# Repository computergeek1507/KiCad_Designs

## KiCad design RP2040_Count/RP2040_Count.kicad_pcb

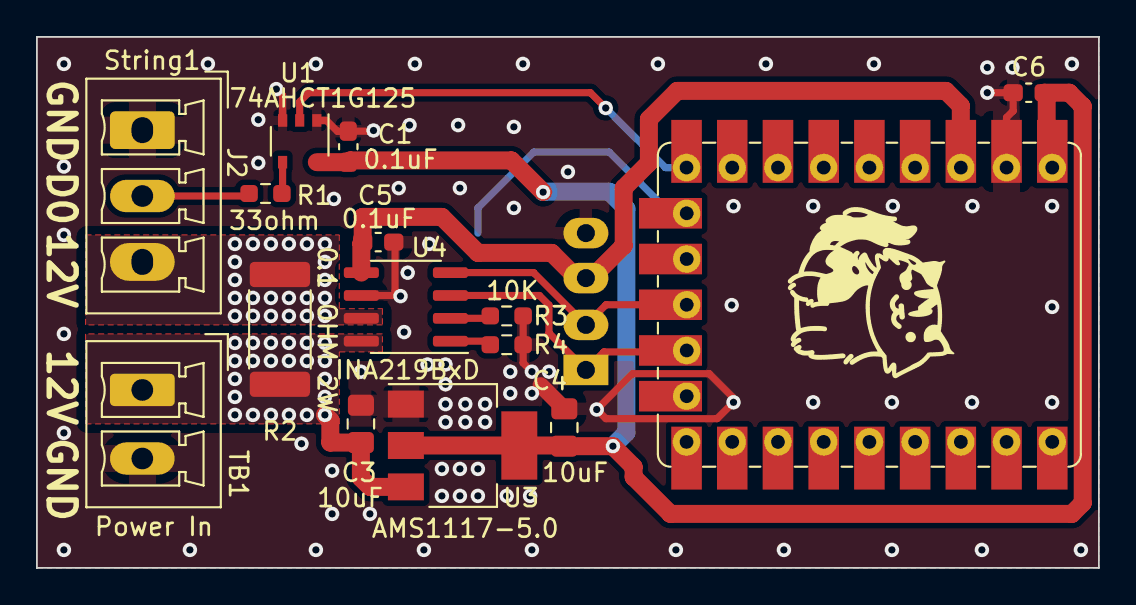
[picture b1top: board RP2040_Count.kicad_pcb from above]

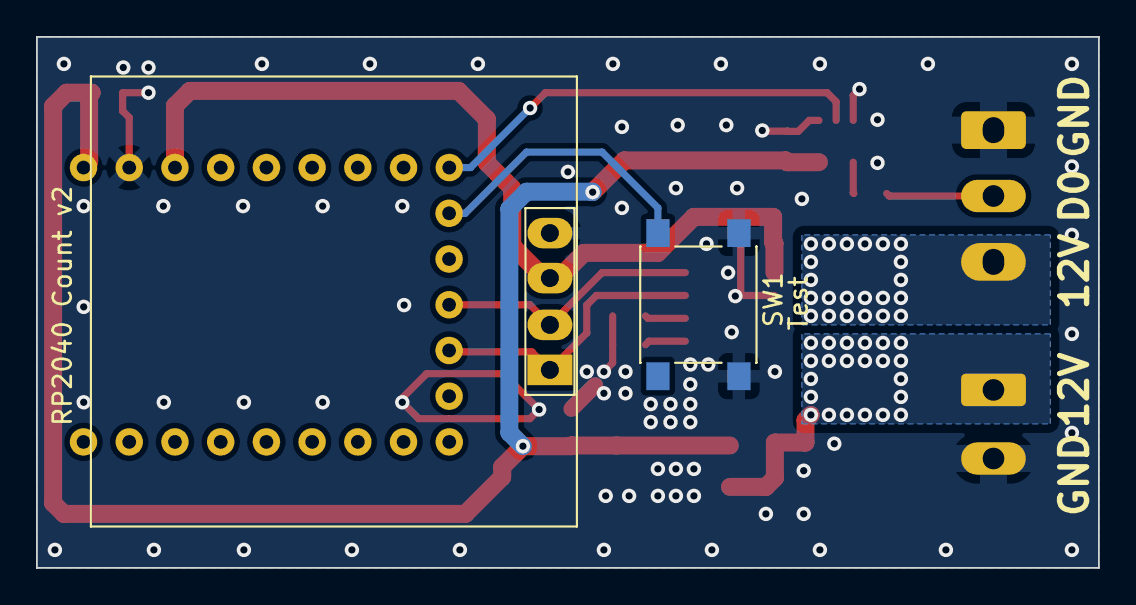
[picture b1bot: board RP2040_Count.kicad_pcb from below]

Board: 2 copper layers, 59.0 x 29.5 mm, 17 parts (2 on the bottom side), 13 nets.

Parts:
C1, C5, C6: 0.1uF; C_0603_1608Metric_Pad1.08x0.95mm_HandSolder
C3, C4: 10uF; C_0805_2012Metric_Pad1.18x1.45mm_HandSolder
J2: String1; PhoenixContact_MCV_3.81mm_3.5mm_1x03_Vertical
J3: OLED; OLED-SSD1306-128X64-I2C-THT_SCOTT2
R1: 33ohm; R_0603_1608Metric_Pad0.98x0.95mm_HandSolder
R2: 0.1 OHM 2W; R_2512_6332Metric_Pad1.40x3.35mm_HandSolder
R3, R4: 10K; R_0603_1608Metric_Pad0.98x0.95mm_HandSolder
SW1: Test; SW_Push_1P1T_NO_6x6mm_H9.5mm
TB1: Power In; PhoenixContact_MCV_1,5_2-G-3.81_1x02_P3.81mm_Vertical
U1: 74AHCT1G125; TSOP-5_1.65x3.05mm_P0.95mm
U3: AMS1117-5.0; SOT-223-3_TabPin2
U4: INA219BxD; SOIC-8_3.9x4.9mm_P1.27mm
U5: RP2040-Tiny; RP2040-Tiny_Scott

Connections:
+3.3V: C5.1, J3.3, U4.5 (VS), U5.3 (3V3)
+5V: C1.1, C4.1, C6.2, U1.5 (VCC), U3.2 (VO), U5.1 (5V)
/DOUT1: J2.2, R1.1
GND: C1.2, C3.2, C4.2, C5.2, C6.1, J2.1, J3.4, R3.2, R4.2, SW1.2, TB1.2, U1.1, U1.3 (GND), U3.1 (GND), U4.6 (GND), U5.2 (GND)
I2C_SCL: J3.2, U4.4 (SCL), U5.12 (GPIO11)
I2C_SDA: J3.1, U4.3 (SDA), U5.13 (GPIO10)
unnamed: R1.2, U1.4
unnamed: R3.1, U4.2 (A0)
unnamed: R4.1, U4.1 (A1)
OUT1: U1.2, U5.9 (GPIO14)
SW1: SW1.1, U5.10 (GPIO13)
VIN1: C3.1, R2.1, TB1.1, U3.3 (VI), U4.8 (IN+)
VOUT1: J2.3, R2.2, U4.7 (IN-)

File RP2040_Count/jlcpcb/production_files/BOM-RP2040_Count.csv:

Comment,Designator,Footprint,LCSC
INA219BxD,U4,SOIC-8_3.9x4.9mm_P1.27mm,C138706
0.1uF,"C1,C5,C6",C_0603_1608Metric_Pad1.08x0.95mm_HandSolder,C14663
10uF,"C3,C4",C_0805_2012Metric_Pad1.18x1.45mm_HandSolder,C15850
33ohm,R1,R_0603_1608Metric_Pad0.98x0.95mm_HandSolder,C23140
10K,"R3,R4",R_0603_1608Metric_Pad0.98x0.95mm_HandSolder,C25804
Test,SW1,SW_Push_1P1T_NO_6x6mm_H9.5mm,C2834918
0.1 OHM 2W,R2,R_2512_6332Metric_Pad1.40x3.35mm_HandSolder,C2903476
AMS1117-5.0,U3,SOT-223-3_TabPin2,C6187
74AHCT1G125,U1,TSOP-5_1.65x3.05mm_P0.95mm,C7484

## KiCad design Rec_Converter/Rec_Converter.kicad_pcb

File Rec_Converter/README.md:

# Copyright and Disclaimer
Copyright: Scott Hanson

This documentation describes Open Hardware and is licensed under the CERN OHL v. 1.2.

You may redistribute and modify this documentation under the terms of the CERN OHL v.1.2. (http://ohwr.org/cernohl). This documentation is distributed WITHOUT ANY EXPRESS OR IMPLIED WARRANTY, INCLUDING OF MERCHANTABILITY, SATISFACTORY QUALITY AND FITNESS FOR A PARTICULAR PURPOSE. Please see the CERN OHL v.1.2 for applicable conditions

# Rec Converter

Converter to use HolidayCoro dumb reciever with Falcon/Kulp Controllers and vice versa. The design was made with all through hole components for easy assembly by most users. Open source applications were used to create this controller. [KiCad](http://kicad-pcb.org/) was used for the PCB design, and [LibreOffice](https://www.libreoffice.org/) for the documentation.

To order your own PCB upload the gerber.zip file to your favorite PCB manufacture of choice, I personally use [jlcpcb.com](https://jlcpcb.com/).

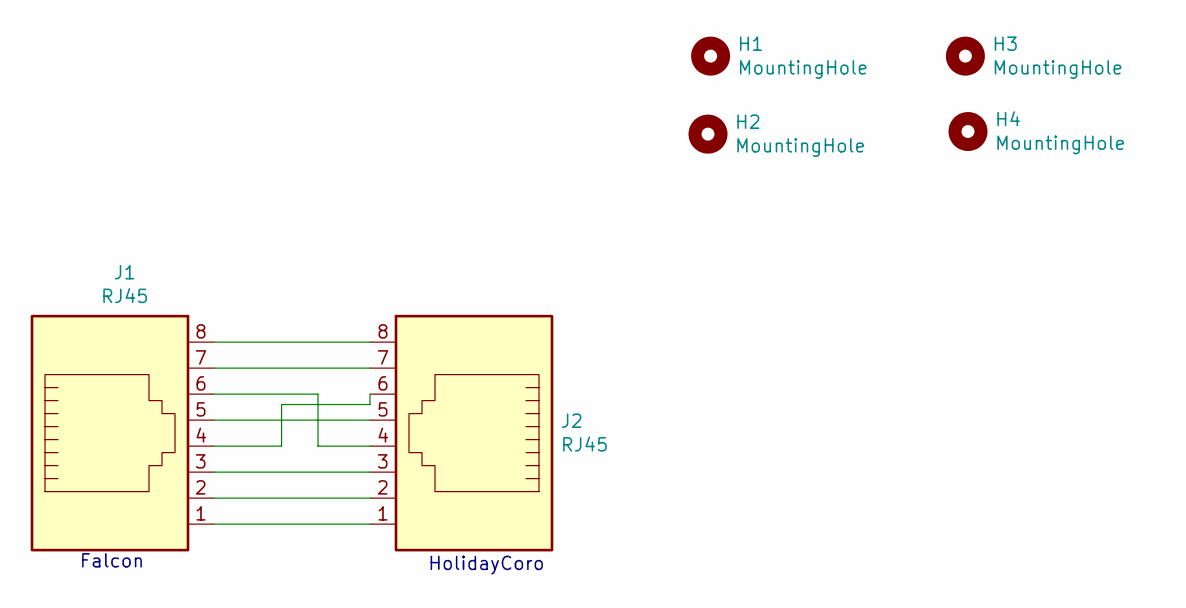
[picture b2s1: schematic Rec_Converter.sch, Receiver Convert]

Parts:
H1, H2, H3, H4: MountingHole; MountingHole_3.5mm
J1, J2: RJ45; RJ45_Amphenol_54602-x08_Horizontal; MPN A-2014-2-4-R; Digi-Key_PN AE10392-ND

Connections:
unnamed: J1.1, J2.1
unnamed: J1.2, J2.2
unnamed: J1.3, J2.3
unnamed: J1.4, J2.6
unnamed: J1.5, J2.5
unnamed: J1.6, J2.4
unnamed: J1.7, J2.7
unnamed: J1.8, J2.8

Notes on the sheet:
HolidayCoro
Falcon

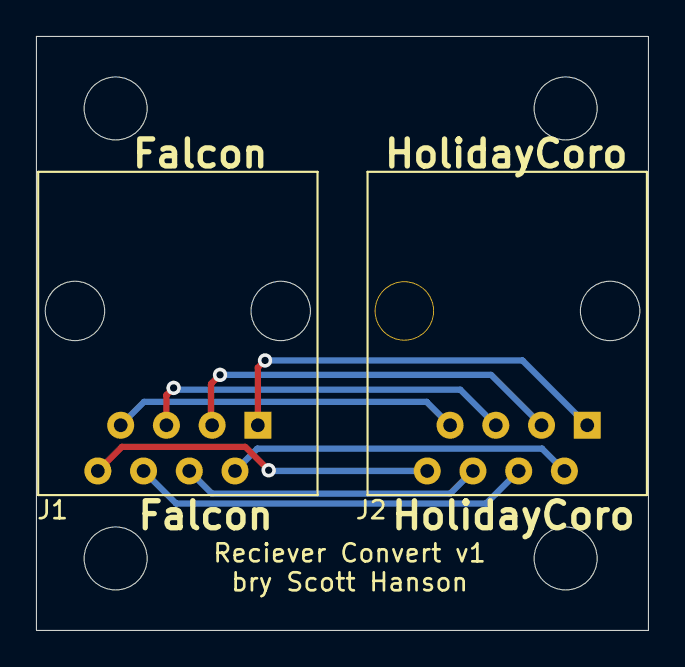
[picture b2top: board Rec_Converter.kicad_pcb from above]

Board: 2 copper layers, 34.0 x 33.0 mm, 6 parts (0 on the bottom side), 8 nets.

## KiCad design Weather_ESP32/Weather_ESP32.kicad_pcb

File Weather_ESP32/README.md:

# Copyright and Disclaimer
Copyright: Scott Hanson

This documentation describes Open Hardware and is licensed under the CERN OHL v. 1.2.

You may redistribute and modify this documentation under the terms of the CERN OHL v.1.2. (http://ohwr.org/cernohl). This documentation is distributed WITHOUT ANY EXPRESS OR IMPLIED WARRANTY, INCLUDING OF MERCHANTABILITY, SATISFACTORY QUALITY AND FITNESS FOR A PARTICULAR PURPOSE. Please see the CERN OHL v.1.2 for applicable conditions

# Weather ESP32

Breakout board for the WT32-ETH01 to use it with the [Sparkfun Weather Meter Kit](https://www.sparkfun.com/products/15901). The design was made with all through hole components for easy assembly by most users. Open source applications were used to create this controller. [KiCad](http://kicad-pcb.org/) was used for the PCB design, and [LibreOffice](https://www.libreoffice.org/) for the documentation.

To order your own PCB upload the gerber.zip file to your favorite PCB manufacture of choice, I personally use [jlcpcb.com](https://jlcpcb.com/).

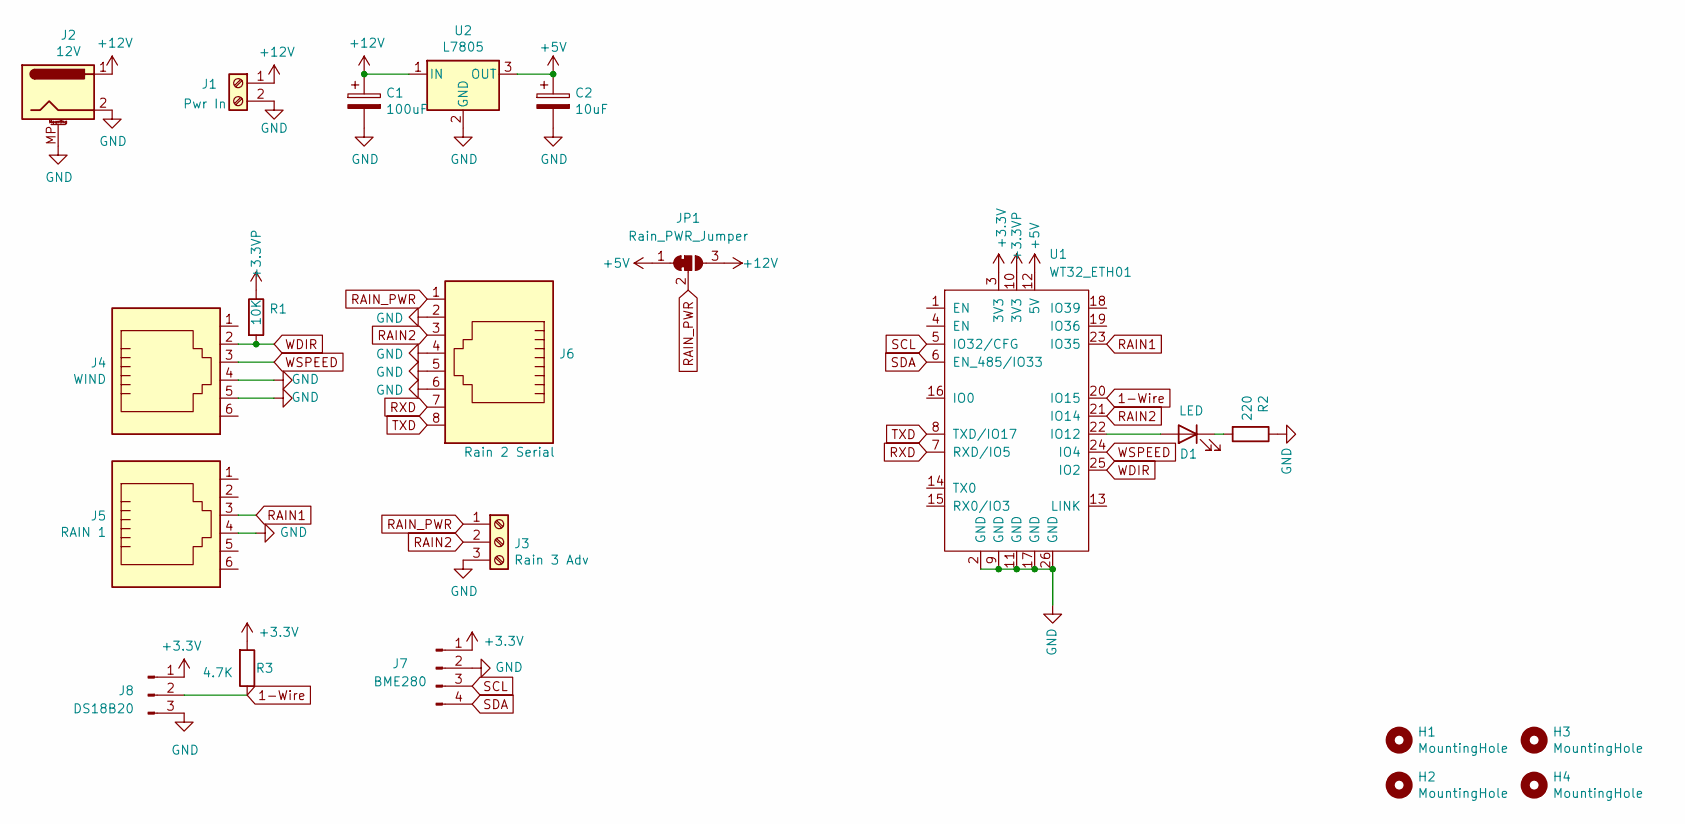
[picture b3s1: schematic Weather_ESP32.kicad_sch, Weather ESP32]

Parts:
C1: 100uF; CP_Radial_D5.0mm_P2.50mm
C2: 10uF; CP_Radial_D5.0mm_P2.50mm
D1: LED; LED_D3.0mm; MPN 150080RS75000; Digi-Key_PN 732-4984-1-ND
H1, H2, H3, H4: MountingHole; MountingHole_3.7mm
J1: Pwr In; TerminalBlock_Phoenix_MKDS-1,5-2_1x02_P5.00mm_Horizontal
J2: 12V; BarrelJack_Horizontal
J3: Rain 3 Adv; TerminalBlock_Phoenix_MKDS-1,5-3_1x03_P5.00mm_Horizontal
J4: WIND; RJ12_Amphenol_54601; Digikey AE10391-ND
J5: RAIN 1; RJ12_Amphenol_54601; Digikey AE10391-ND
J6: Rain 2 Serial; RJ45_Amphenol_54602-x08_Horizontal
J7: BME280; PinHeader_1x04_P2.54mm_Vertical
J8: DS18B20; JST_XH_B3B-XH-A_1x03_P2.50mm_Vertical
JP1: Rain_PWR_Jumper; SolderJumper-3_P1.3mm_Bridged2Bar12_RoundedPad1.0x1.5mm_Num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
R1: 10K; R_Axial_DIN0207_L6.3mm_D2.5mm_P7.62mm_Horizontal
R2: 220; R_Axial_DIN0207_L6.3mm_D2.5mm_P7.62mm_Horizontal; MPN RMCF0603FT220R; Digi-Key_PN RMCF0603FT220RTR-ND
R3: 4.7K; R_Axial_DIN0207_L6.3mm_D2.5mm_P7.62mm_Horizontal
U1: WT32_ETH01
U2: L7805; TO-220-3_Vertical

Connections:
1-Wire: J8.2, R3.1, U1.20 (IO15)
+3.3VP: R1.1, U1.10 (3V3)
+3V3: J7.1, J8.1, R3.2, U1.3 (3V3)
+5V: C2.1, JP1.1 (A), U1.12 (5V), U2.3 (OUT)
+12V: C1.1, J1.1, J2.1, JP1.3 (B), U2.1 (IN)
GND: C1.2, C2.2, J1.2, J2.2, J2.MP (MountPin), J3.3, J4.4, J4.5, J5.4, J6.2, J6.4, J6.5, J6.6, J7.2, J8.3, R2.1, U1.2 (GND), U1.9 (GND), U1.11 (GND), U1.17 (GND), U1.26 (GND), U2.2 (GND)
unnamed: D1.2 (A), U1.22 (IO12)
unnamed: D1.1 (K), R2.2
RAIN1: J5.3, U1.23 (IO35)
RAIN2: J3.2, J6.3, U1.21 (IO14)
RAIN_PWR: J3.1, J6.1, JP1.2 (C)
RXD: J6.7, U1.7 (RXD/IO5)
SCL: J7.3, U1.5 (IO32/CFG)
SDA: J7.4, U1.6 (EN_485/IO33)
TXD: J6.8, U1.8 (TXD/IO17)
WDIR: J4.2, R1.2, U1.25 (IO2)
WSPEED: J4.3, U1.24 (IO4)

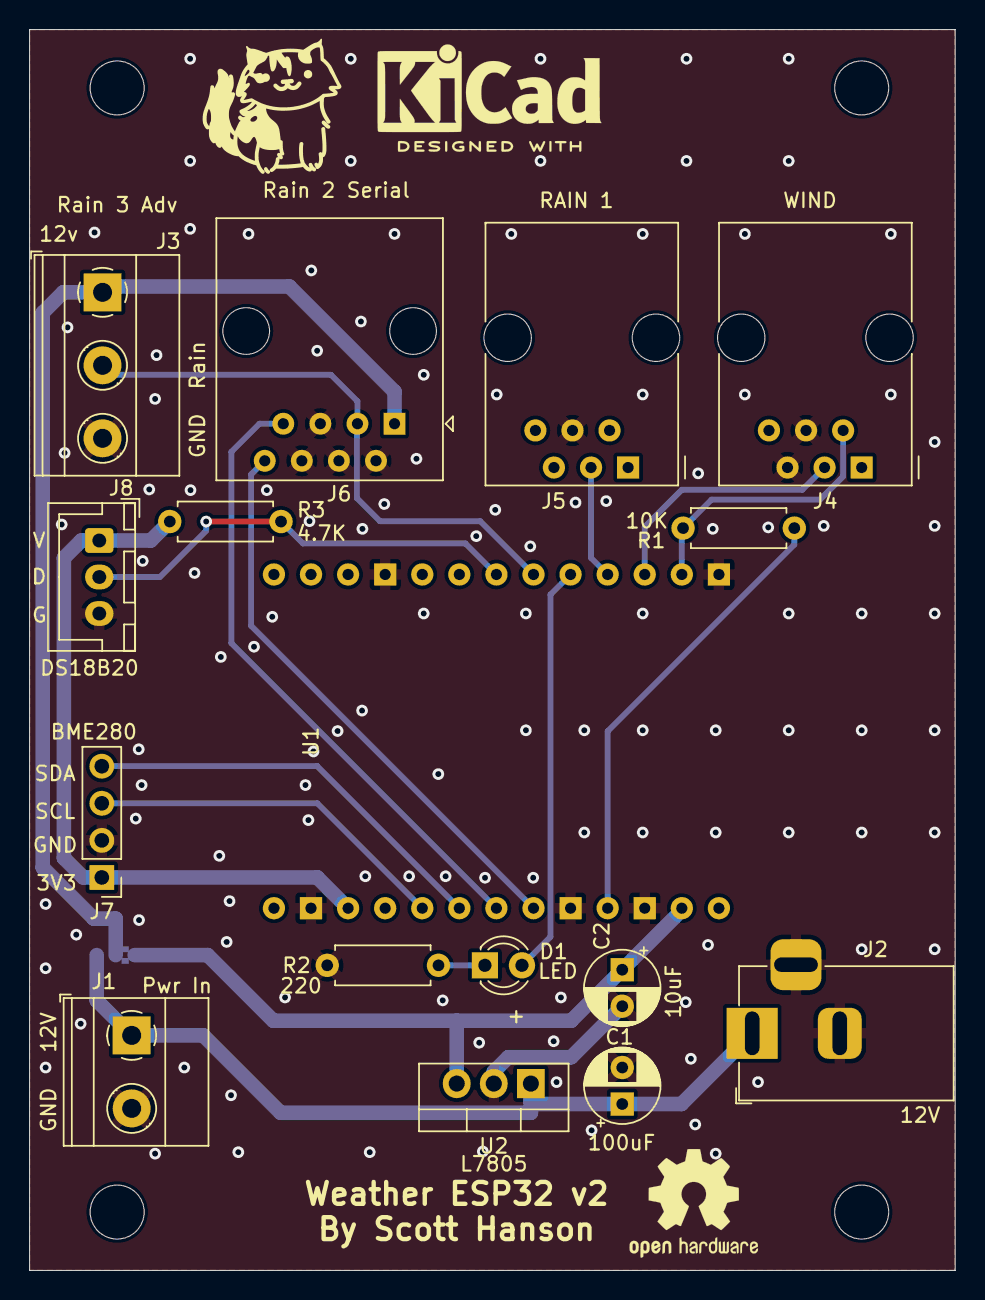
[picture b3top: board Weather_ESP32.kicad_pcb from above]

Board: 2 copper layers, 63.4 x 85.0 mm, 21 parts (1 on the bottom side), 17 nets.

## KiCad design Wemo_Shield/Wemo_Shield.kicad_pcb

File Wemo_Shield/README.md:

# Copyright and Disclaimer
Copyright: Scott Hanson

This documentation describes Open Hardware and is licensed under the CERN OHL v. 1.2.

You may redistribute and modify this documentation under the terms of the CERN OHL v.1.2. (http://ohwr.org/cernohl). This documentation is distributed WITHOUT ANY EXPRESS OR IMPLIED WARRANTY, INCLUDING OF MERCHANTABILITY, SATISFACTORY QUALITY AND FITNESS FOR A PARTICULAR PURPOSE. Please see the CERN OHL v.1.2 for applicable conditions

# Wemo Shield

Wemo D1 Mini Breakout board. The design was made with all through hole components for easy assembly by most users. Open source applications were used to create this PCB. [KiCad](http://kicad-pcb.org/) was used for the PCB design, and [LibreOffice](https://www.libreoffice.org/) for the documentation.

To order your own PCB upload the gerber.zip file to your favorite PCB manufacture of choice, I personally use [jlcpcb.com](https://jlcpcb.com/).

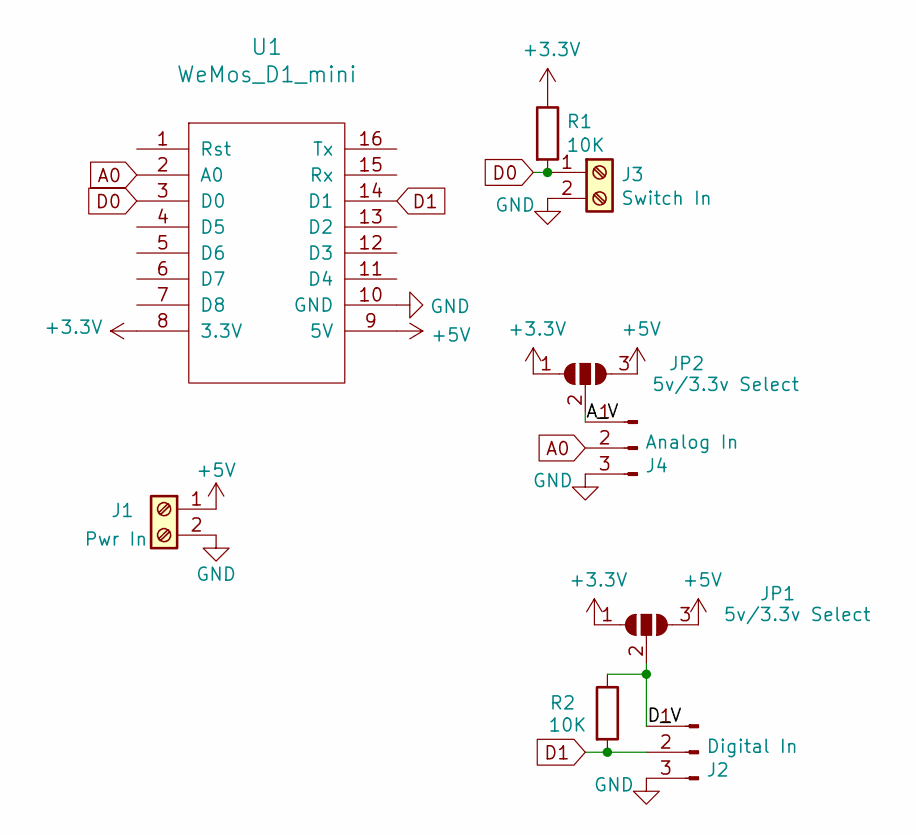
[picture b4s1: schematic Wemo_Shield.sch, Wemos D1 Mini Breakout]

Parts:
J1: Pwr In; TerminalBlock_Phoenix_MKDS-1,5-2_1x02_P5.00mm_Horizontal
J2: Digital In; PinHeader_1x03_P2.54mm_Horizontal
J3: Switch In; TerminalBlock_Phoenix_MKDS-1,5-2_1x02_P5.00mm_Horizontal
J4: Analog In; PinHeader_1x03_P2.54mm_Horizontal
JP1, JP2: 5v/3.3v Select; SolderJumper-3_P1.3mm_Open_Pad1.0x1.5mm
R1, R2: 10K; R_0805_2012Metric_Pad1.15x1.40mm_HandSolder
U1: WeMos_D1_mini; wemos-d1-mini-connectors-only

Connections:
+3V3: JP1.1 (A), JP2.1 (A), R1.1, U1.8 (3.3V)
+5V: J1.1, JP1.3 (B), JP2.3 (B), U1.9 (5V)
/A_V: J4.1, JP2.2 (C)
/D_V: J2.1, JP1.2 (C), R2.1
A0: J4.2, U1.2 (A0)
D0: J3.1, R1.2, U1.3 (D0)
D1: J2.2, R2.2, U1.14 (D1)
GND: J1.2, J2.3, J3.2, J4.3, U1.10 (GND)

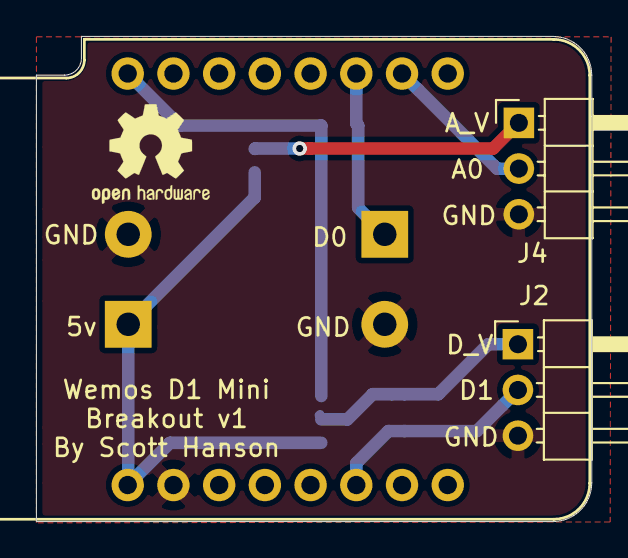
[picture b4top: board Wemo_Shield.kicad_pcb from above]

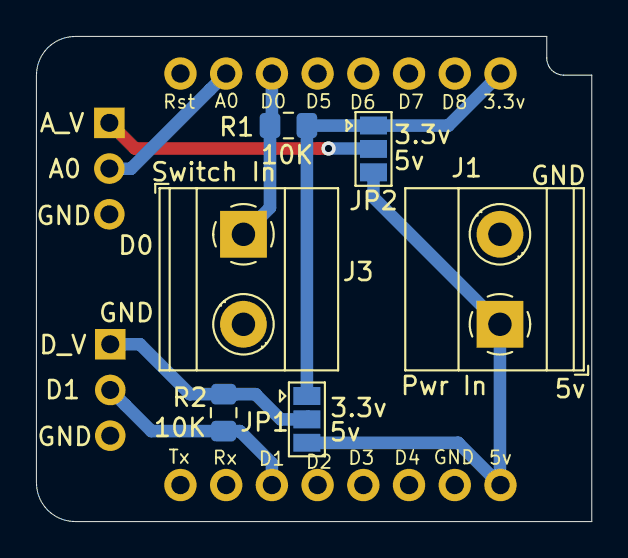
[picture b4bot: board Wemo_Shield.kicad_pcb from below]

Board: 2 copper layers, 30.9 x 27.0 mm, 9 parts (6 on the bottom side), 8 nets.
